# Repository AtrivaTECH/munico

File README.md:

# μNico
All files for the μNico Project!

## Licensing

## Tools Utilised

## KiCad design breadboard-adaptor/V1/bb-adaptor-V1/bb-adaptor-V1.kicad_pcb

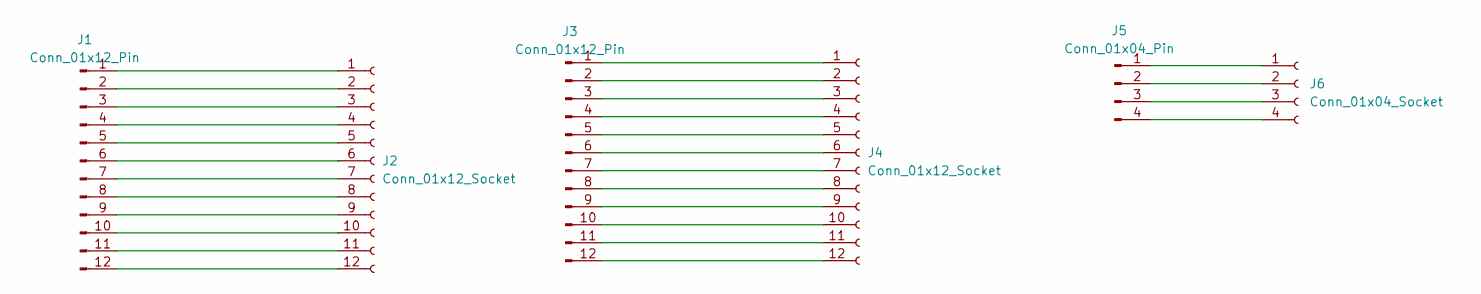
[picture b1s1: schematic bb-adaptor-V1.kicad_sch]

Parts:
J1, J3: Conn_01x12_Pin; PinHeader_1x12_P2.54mm_Vertical
J2, J4: Conn_01x12_Socket; pads__1x12
J5: Conn_01x04_Pin; pads__1x04
J6: Conn_01x04_Socket; PinHeader_1x04_P2.54mm_Vertical

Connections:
unnamed: J1.1, J2.1
unnamed: J1.2, J2.2
unnamed: J1.3, J2.3
unnamed: J1.4, J2.4
unnamed: J1.5, J2.5
unnamed: J1.6, J2.6
unnamed: J1.7, J2.7
unnamed: J1.8, J2.8
unnamed: J1.9, J2.9
unnamed: J1.10, J2.10
unnamed: J1.11, J2.11
unnamed: J1.12, J2.12
unnamed: J3.1, J4.1
unnamed: J3.2, J4.2
unnamed: J3.3, J4.3
unnamed: J3.4, J4.4
unnamed: J3.5, J4.5
unnamed: J3.6, J4.6
unnamed: J3.7, J4.7
unnamed: J3.8, J4.8
unnamed: J3.9, J4.9
unnamed: J3.10, J4.10
unnamed: J3.11, J4.11
unnamed: J3.12, J4.12
unnamed: J5.1, J6.1
unnamed: J5.2, J6.2
unnamed: J5.3, J6.3
unnamed: J5.4, J6.4

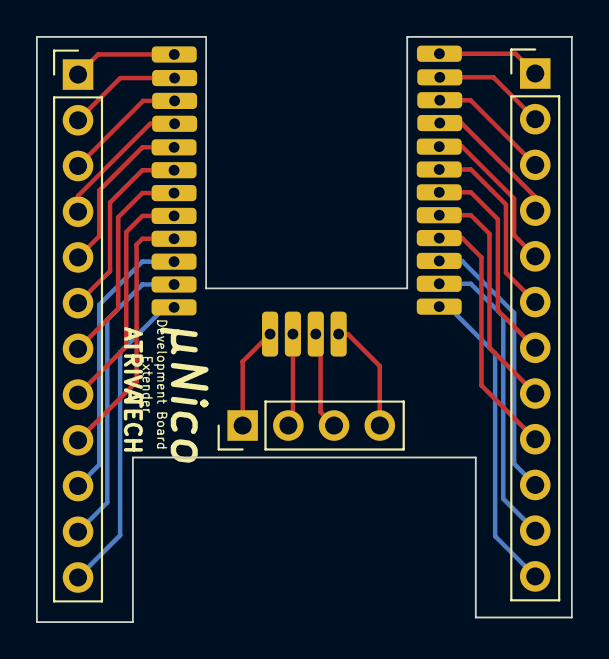
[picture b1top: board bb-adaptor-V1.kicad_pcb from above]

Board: 2 copper layers, 29.7 x 32.5 mm, 6 parts (0 on the bottom side), 28 nets.

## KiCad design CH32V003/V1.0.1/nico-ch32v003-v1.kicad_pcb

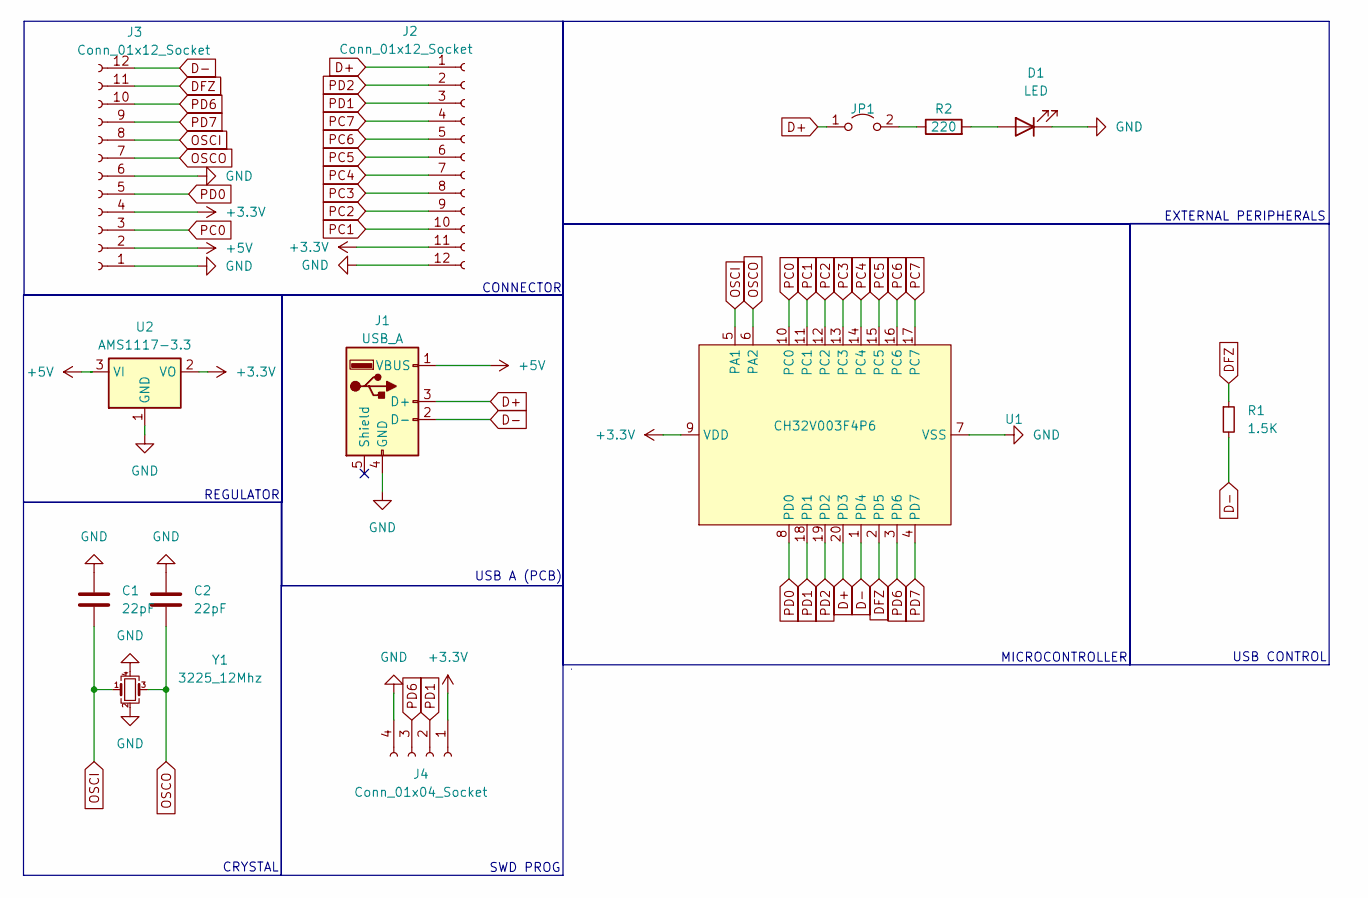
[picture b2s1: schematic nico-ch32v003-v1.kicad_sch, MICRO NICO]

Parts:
C1, C2: 22pF; C_0402_1005Metric_Pad0.74x0.62mm_HandSolder
D1: LED; LED_0603_1608Metric
J1: USB_A; usb-PCB
J2, J3: Conn_01x12_Socket; pads-1*12
J4: Conn_01x04_Socket; pads__1x04
JP1: Jumper_2_Open; jumper-2-open
R1: 1.5K; R_0402_1005Metric_Pad0.72x0.64mm_HandSolder
R2: 220; R_0402_1005Metric
U1: CH32V003F4P6; TSSOP-20_4.4x6.5mm_P0.65mm
U2: AMS1117-3.3; SOT-223-3_TabPin2
Y1: 3225_12Mhz; Crystal_SMD_3225-4Pin_3.2x2.5mm

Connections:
+3.3V: J2.11, J3.4, J4.1, U1.9 (VDD), U2.2 (VO)
+5V: J1.1 (VBUS), J3.2, U2.3 (VI)
D+: J1.3 (D+), J2.1, JP1.1 (A), U1.20 (PD3)
D-: J1.2 (D-), J3.12, R1.2, U1.1 (PD4)
DFZ: J3.11, R1.1, U1.2 (PD5)
GND: C1.1, C2.1, D1.1 (K), J1.4 (GND), J2.12, J3.1, J3.6, J4.4, U1.7 (VSS), U2.1 (GND), Y1.2, Y1.4
unnamed: D1.2 (A), R2.2
unnamed: JP1.2 (B), R2.1
OSCI: C1.2, J3.8, U1.5 (PA1), Y1.1
OSCO: C2.2, J3.7, U1.6 (PA2), Y1.3
PC0: J3.3, U1.10 (PC0)
PC1: J2.10, U1.11 (PC1)
PC2: J2.9, U1.12 (PC2)
PC3: J2.8, U1.13 (PC3)
PC4: J2.7, U1.14 (PC4)
PC5: J2.6, U1.15 (PC5)
PC6: J2.5, U1.16 (PC6)
PC7: J2.4, U1.17 (PC7)
PD0: J3.5, U1.8 (PD0)
PD1: J2.3, J4.2, U1.18 (PD1)
PD2: J2.2, U1.19 (PD2)
PD6: J3.10, J4.3, U1.3 (PD6)
PD7: J3.9, U1.4 (PD7)

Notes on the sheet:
USB A (PCB)
SWD PROG
REGULATOR
CONNECTOR
CRYSTAL
EXTERNAL PERIPHERALS
MICROCONTROLLER
USB CONTROL

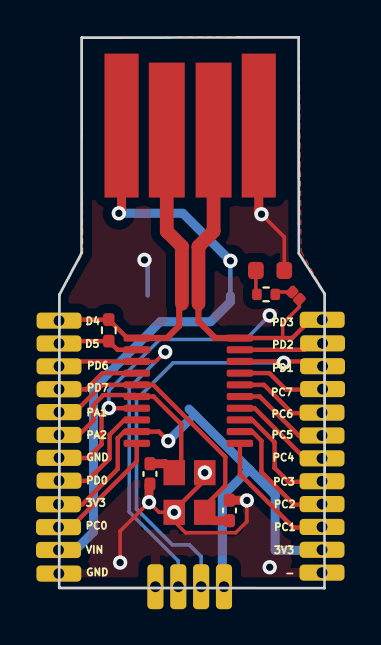
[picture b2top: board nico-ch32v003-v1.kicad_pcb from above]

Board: 2 copper layers, 14.7 x 30.6 mm, 13 parts (1 on the bottom side), 23 nets.

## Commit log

2024-05-19 KiCad Files for V1
2024-05-19 Gerber Files for V1 Micro nico
2024-05-19 All files for 1.0.1 uploaded.
    File directory format changed.
2024-05-19 1.0.1 gerbers
